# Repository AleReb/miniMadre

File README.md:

# miniMadre

**Placa de desarrollo basada en el trabajo de Sebastian Adonay con Alejandro Rebolledo.**

## Descripción del Proyecto

El objetivo de este proyecto es desarrollar una versión miniatura y flexible de una placa madre (*motherboard*) que también funcione como una placa para el **hiriPro**.

### Características Principales

*   **Versatilidad:** Diseñada para ser una solución miniatura y flexible.
*   **Integración ESP32-S3:** Se remplaza el uso de chips FTDI por el uso directo del **ESP32-S3**, aprovechando sus capacidades nativas de USB y mayor potencia de procesamiento.
*   **Expansión Flexible:** Incorpora un conector flexible diseñado específicamente para sacar placas hijo (*daughter boards*), permitiendo una gran modularidad y adaptabilidad a diferentes proyectos.

---
*Este proyecto es una evolución colaborativa buscando optimizar espacio y funcionalidad.*

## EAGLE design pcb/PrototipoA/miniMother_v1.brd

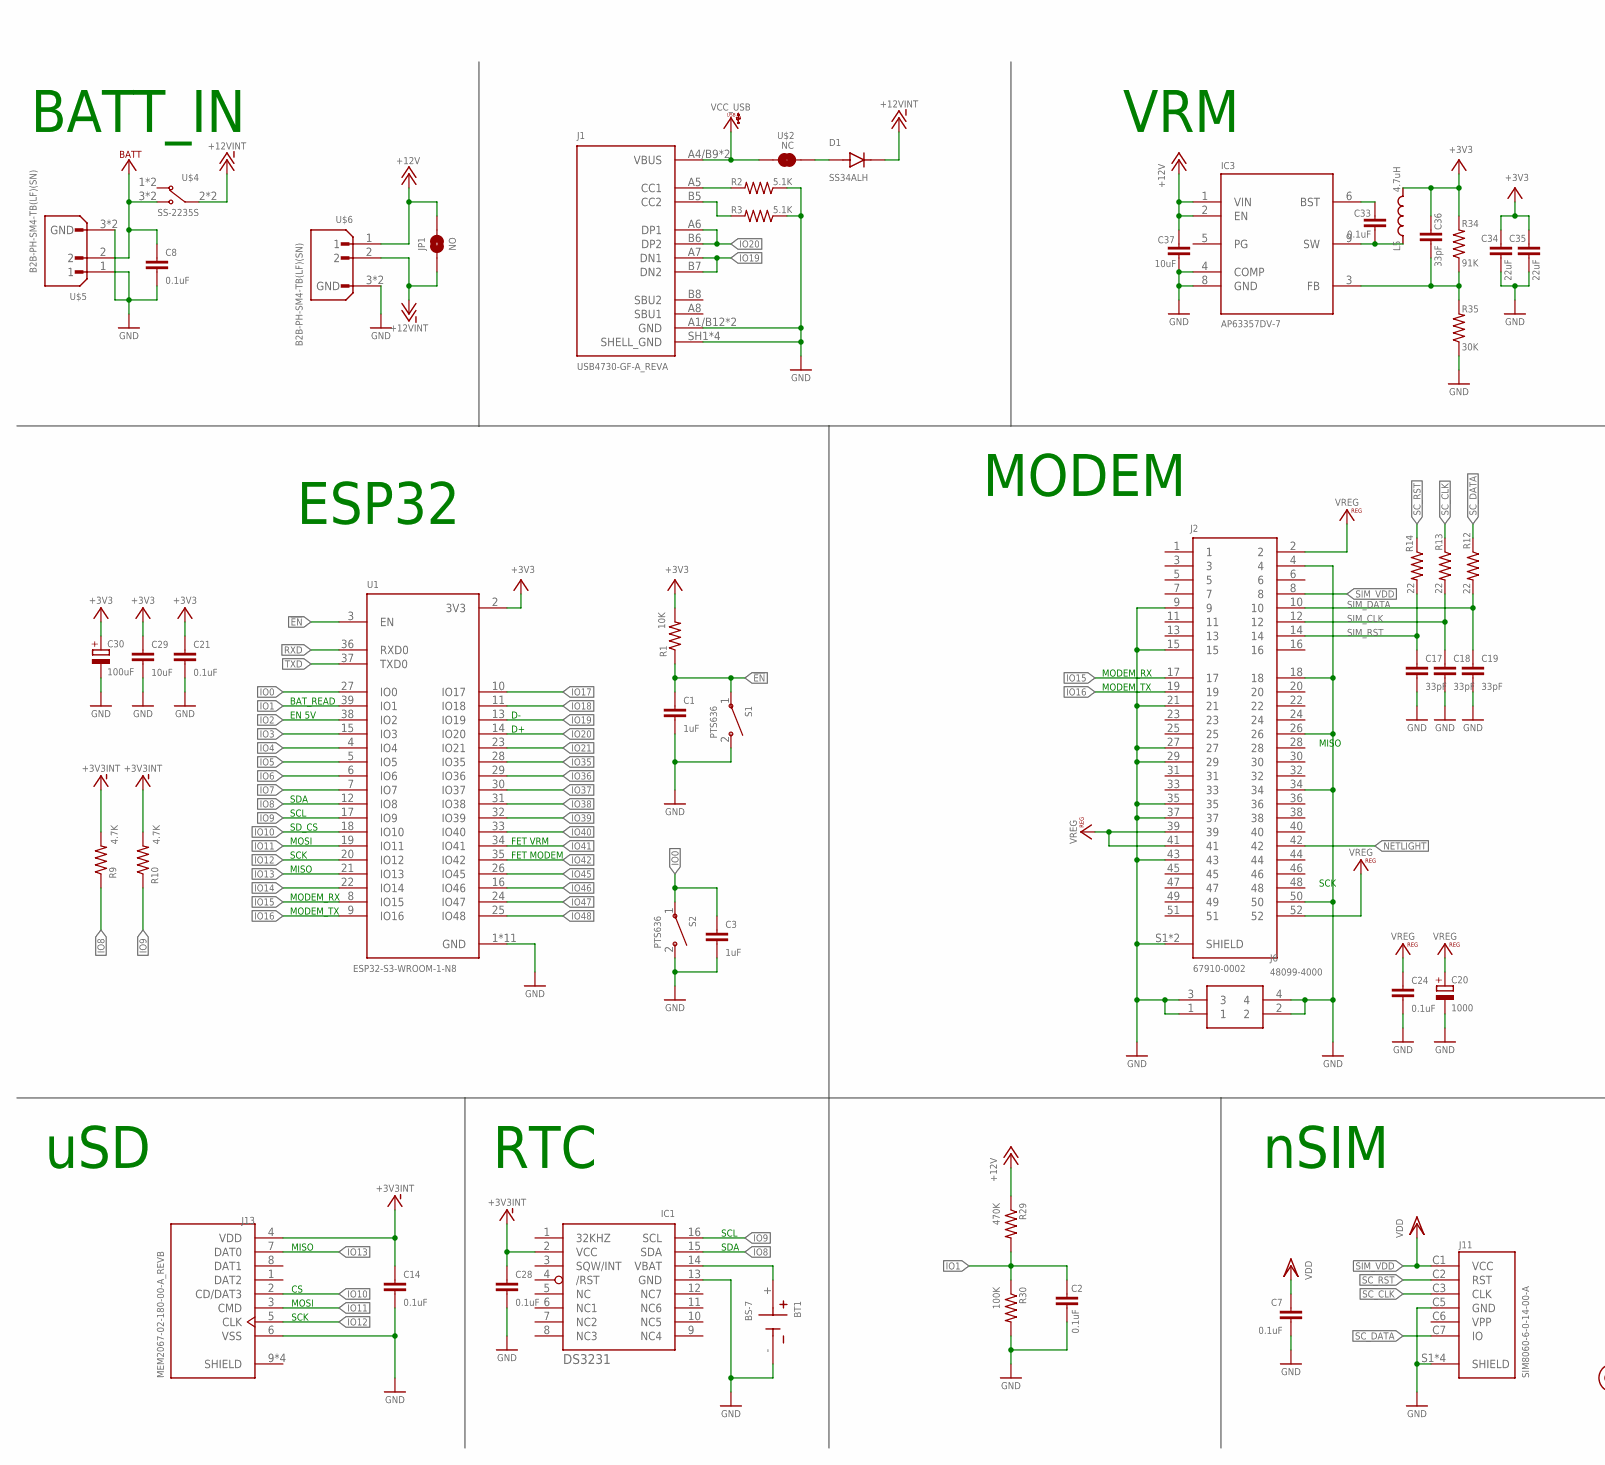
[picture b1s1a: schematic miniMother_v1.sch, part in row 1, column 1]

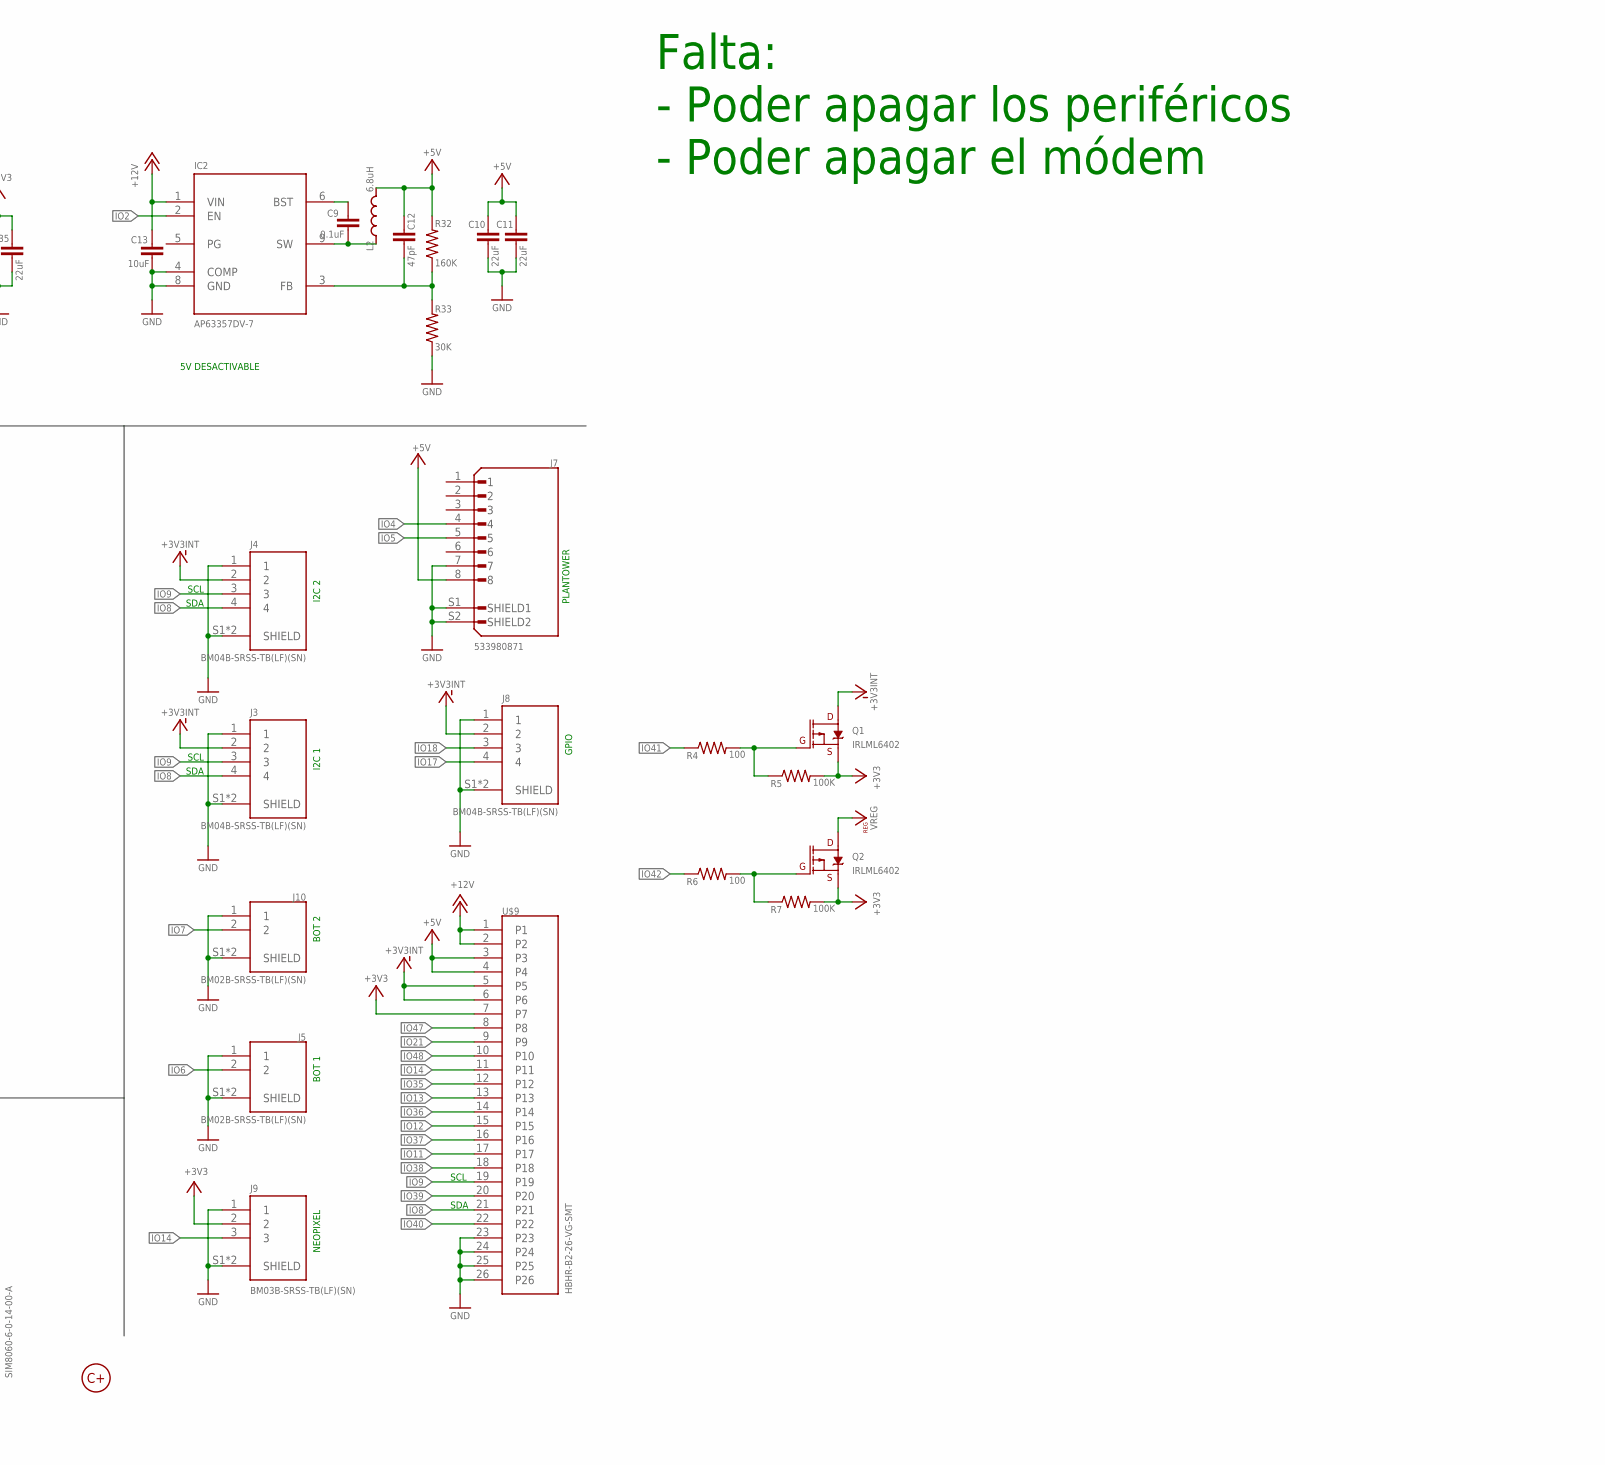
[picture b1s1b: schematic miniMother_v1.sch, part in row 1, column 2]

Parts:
BT1: BS-7; BAT_BS-7
C1, C3: 1uF; C0805
C2, C7, C8, C9, C14, C21, C24, C28, C33: 0.1uF; C0805
C10, C11, C34, C35: 22uF; C0805
C12: 47pF; C0805
C13, C29, C37: 10uF; C0805
C17, C18, C19, C36: 33pF; C0805
C20: 1000; SMC_D
C30: 100uF; CT3528
D1: SS34ALH; SODFL5226X100N
IC1: DS3231/SO; SO16W
IC2, IC3: AP63357DV-7; AP63357DV7
J1: USB4730-GF-A_REVA; GCT_USB4730-GF-A_REVA
J2: 67910-0002; MOLEX_67910-0002
J3, J4, J8: BM04B-SRSS-TB(LF)(SN); JST_BM04B-SRSS-TB(LF)(SN)
J5, J10: BM02B-SRSS-TB(LF)(SN); JST_BM02B-SRSS-TB(LF)(SN)
J6: 48099-4000; 480994000
J7: 533980871; MOLEX_533980871
J9: BM03B-SRSS-TB(LF)(SN); JST_BM03B-SRSS-TB(LF)(SN)
J11: SIM8060-6-0-14-00-A; GCT_SIM8060-6-0-14-00-A
J13: MEM2067-02-180-00-A_REVB; GCT_MEM2067-02-180-00-A_REVB
JP1: NO; SMT-JUMPER_2_NO_NO-SILK_ROUND
L2: 6.8uH; IND_MDH7045C-220MA=P3
L5: 4.7uH; IND_MDH7045C-220MA=P3
Q1, Q2: IRLML6402; SOT23-3
R1: 10K; R0805
R2, R3: 5.1K; R0805
R4, R6: 100; R0805
R5, R7, R30: 100K; R0805
R9, R10: 4.7K; R0805
R12, R13, R14: 22; R0805
R29: 470K; R0805
R32: 160K; R0805
R33, R35: 30K; R0805
R34: 91K; R0805
S1, S2: PTS636; SW_PTS636_SM43J_SMTR_LFS
U1: ESP32-S3-WROOM-1-N8; XCVR_ESP32-S3-WROOM-1-N8
U$1: LOGO_CMAS10MM; LOGO_10MM
U$2: NC; SMT-JUMPER-2_NC
U$4: SS-2235S
U$5, U$6: B2B-PH-SM4-TB(LF)(SN); JST_B2B-PH-SM4-TB(LF)(SN)
U$9: HBHR-B2-26-VG-SMT

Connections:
!EN: C1.1, R1.1, S1.1 (COM), U1.3 (EN)
+3V3: C21.1, C29.1, C30.+, C34.1, C35.1, C36.1, J9.2, L5.2, Q1.2 (S), Q2.2 (S), R1.2, R5.2, R7.2, R34.2, U1.2 (3V3), U$9.7
+3V3INT: C14.1, C28.1, IC1.2 (VCC), J3.2, J4.2, J8.2, J13.4 (VDD), Q1.3 (D), R9.2, R10.2, U$9.5, U$9.6
+5V: C10.1, C11.1, C12.1, J7.8, L2.2, R32.2, U$9.3, U$9.4
+12V: C13.1, C37.1, IC2.1 (VIN), IC3.1 (VIN), IC3.2 (EN), JP1.1, R29.1, U$6.1, U$9.1, U$9.2
+12VINT: D1.1 (K), JP1.2, U$4.2 (P1), U$4.5 (P1), U$6.2
GND: BT1.-, C1.2, C2.2, C3.2, C7.2, C8.2, C10.2, C11.2, C13.2, C14.2, C17.2, C18.2, C19.2, C20.-, C21.2, C24.2, C28.2, C29.2, C30.-, C34.2, C35.2, C37.2, IC1.13 (GND), IC2.4 (COMP), IC2.8 (GND), IC3.4 (COMP), IC3.8 (GND), J1.A1/B12 (GND), J1.B1/A12 (GND), J1.SH1 (SHELL_GND), J1.SH2 (SHELL_GND), J1.SH3 (SHELL_GND), J1.SH4 (SHELL_GND), J2.4, J2.9, J2.15, J2.18, J2.21, J2.26, J2.27, J2.29, J2.34, J2.35, J2.37, J2.43, J2.50, J2.S1 (SHIELD), J2.S2 (SHIELD), J3.1, J3.S1 (SHIELD), J3.S2 (SHIELD), J4.1, J4.S1 (SHIELD), J4.S2 (SHIELD), J5.1, J5.S1 (SHIELD), J5.S2 (SHIELD), J6.1, J6.2, J6.3, J6.4, J7.7, J7.S1 (SHIELD1), J7.S2 (SHIELD2), J8.1, J8.S1 (SHIELD), J8.S2 (SHIELD), J9.1, J9.S1 (SHIELD), J9.S2 (SHIELD), J10.1, J10.S1 (SHIELD), J10.S2 (SHIELD), J11.C5 (GND), J11.S1 (SHIELD), J11.S2 (SHIELD), J11.S3 (SHIELD), J11.S4 (SHIELD), J13.6 (VSS), R2.1, R3.1, R30.2, R33.1, R35.1, S1.2 (NO), S2.2 (NO), U1.1 (GND), U1.40 (GND), U1.41_1 (GND), U1.41_2 (GND), U1.41_3 (GND), U1.41_4 (GND), U1.41_5 (GND), U1.41_6 (GND), U1.41_7 (GND), U1.41_8 (GND), U1.41_9 (GND), U$5.1, U$5.3 (GND), U$5.4 (GND), U$6.3 (GND), U$6.4 (GND), U$9.23, U$9.24, U$9.25, U$9.26
IO0: C3.1, S2.1 (COM), U1.27 (IO0)
IO1: C2.1, R29.2, R30.1, U1.39 (IO1)
IO2: IC2.2 (EN), U1.38 (IO2)
IO3: U1.15 (IO3)
IO4: J7.4, U1.4 (IO4)
IO5: J7.5, U1.5 (IO5)
IO6: J5.2, U1.6 (IO6)
IO7: J10.2, U1.7 (IO7)
IO8: IC1.15 (SDA), J3.4, J4.4, R9.1, U1.12 (IO8), U$9.21
IO9: IC1.16 (SCL), J3.3, J4.3, R10.1, U1.17 (IO9), U$9.19
IO10: J13.2 (CD/DAT3), U1.18 (IO10)
IO11: J13.3 (CMD), U1.19 (IO11), U$9.17
IO12: J13.5 (CLK), U1.20 (IO12), U$9.15
IO13: J13.7 (DAT0), U1.21 (IO13), U$9.13
IO14: J9.3, U1.22 (IO14), U$9.11
IO15: J2.17, U1.8 (IO15)
IO16: J2.19, U1.9 (IO16)
IO17: J8.4, U1.10 (IO17)
IO18: J8.3, U1.11 (IO18)
IO19: J1.A7 (DN1), J1.B7 (DN2), U1.13 (IO19)
IO20: J1.A6 (DP1), J1.B6 (DP2), U1.14 (IO20)
IO21: U1.23 (IO21), U$9.9
IO35: U1.28 (IO35), U$9.12
IO36: U1.29 (IO36), U$9.14
IO37: U1.30 (IO37), U$9.16
IO38: U1.31 (IO38), U$9.18
IO39: U1.32 (IO39), U$9.20
IO40: U1.33 (IO40), U$9.22
IO41: R4.1, U1.34 (IO41)
IO42: R6.1, U1.35 (IO42)
IO45: U1.26 (IO45)
IO46: U1.16 (IO46)
IO47: U1.24 (IO47), U$9.8
IO48: U1.25 (IO48), U$9.10
unnamed: J1.A5 (CC1), R2.2
unnamed: BT1.+, IC1.14 (VBAT)
unnamed: D1.2 (A), U$2.2
unnamed: Q1.1 (G), R4.2, R5.1
unnamed: J1.B5 (CC2), R3.2
unnamed: Q2.1 (G), R6.2, R7.1
unnamed: C9.1, IC2.6 (BST)
unnamed: C9.2, IC2.9 (SW), L2.1
unnamed: C12.2, IC2.3 (FB), R32.1, R33.2
unnamed: C33.1, IC3.6 (BST)
unnamed: C33.2, IC3.9 (SW), L5.1
unnamed: C36.2, IC3.3 (FB), R34.1, R35.2
NETLIGHT: J2.42
RXD: U1.36 (RXD0)
SC_CLK: J11.C3 (CLK), R13.1
SC_DATA: J11.C7 (IO), R12.1
SC_RST: J11.C2 (RST), R14.1
SIM_CLK: C18.1, J2.12, R13.2
SIM_DATA: C19.1, J2.10, R12.2
SIM_RST: C17.1, J2.14, R14.2
SIM_VDD: C7.1, J2.8, J11.C1 (VCC)
TXD: U1.37 (TXD0)
VBAT: C8.1, U$4.3 (T2), U$4.6 (T2), U$5.2
VCC_USB: J1.A4/B9 (VBUS), J1.B4/A9 (VBUS), U$2.1
VREG: C20.+, C24.1, J2.2, J2.39, J2.41, J2.52, Q2.3 (D)

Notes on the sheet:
VRM
MODEM
ESP32
RTC
nSIM
uSD
BATT_IN
5V DESACTIVABLE
MOSI
SCK
MISO
PLANTOWER
Falta: - Poder apagar los periféricos - Poder apagar el módem
I2C 1
I2C 2
BOT 1
BOT 2
NEOPIXEL
GPIO
SDA
SCL
SD_CS
MODEM_RX
MODEM_TX
EN 5V
BAT_READ
FET VRM
FET MODEM

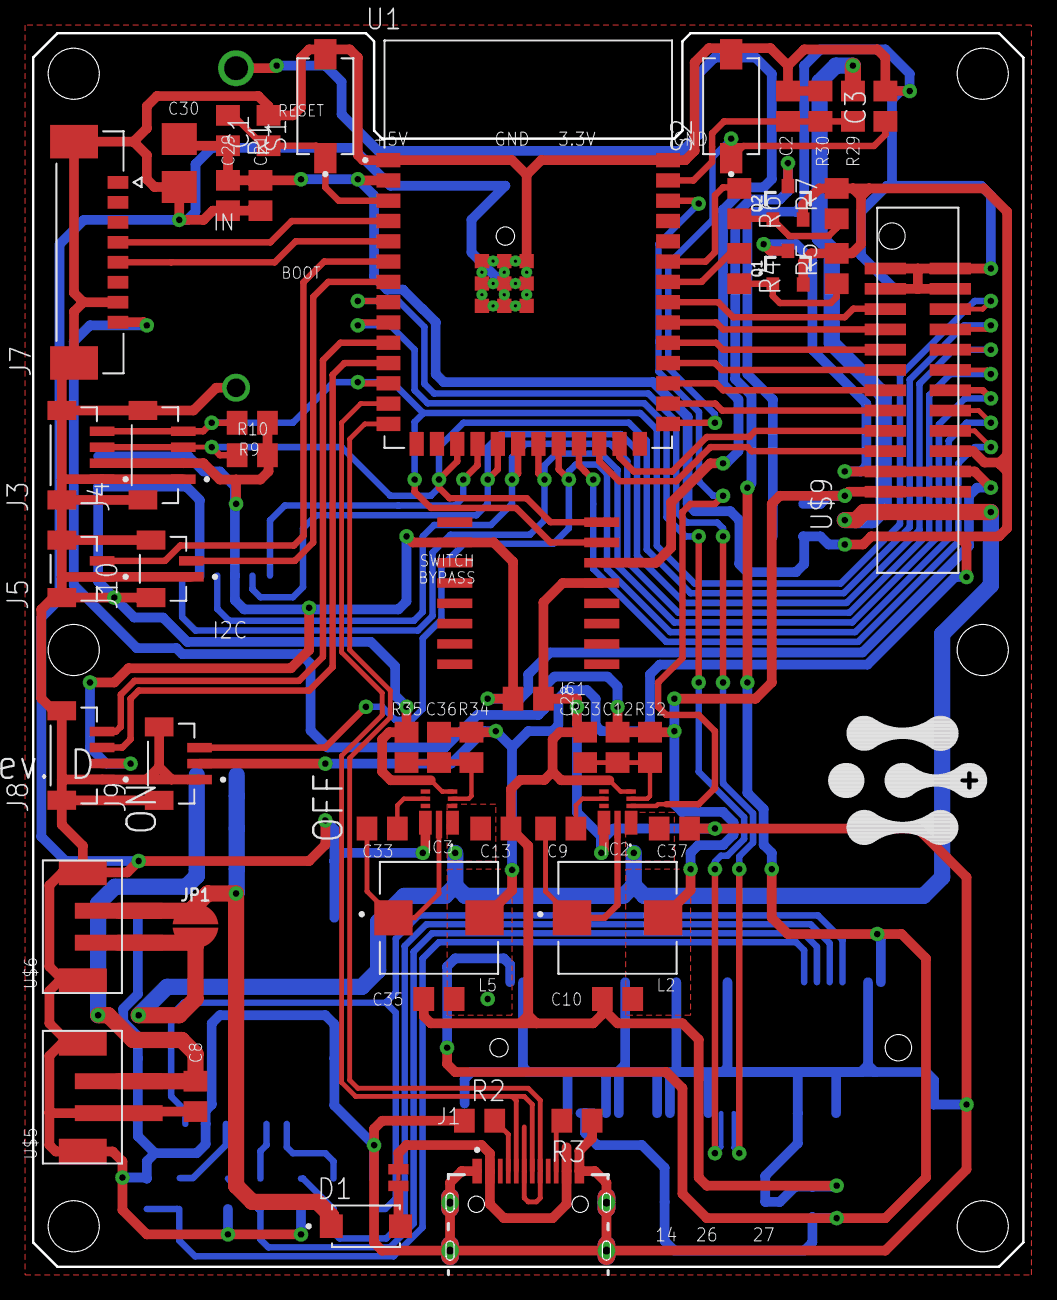
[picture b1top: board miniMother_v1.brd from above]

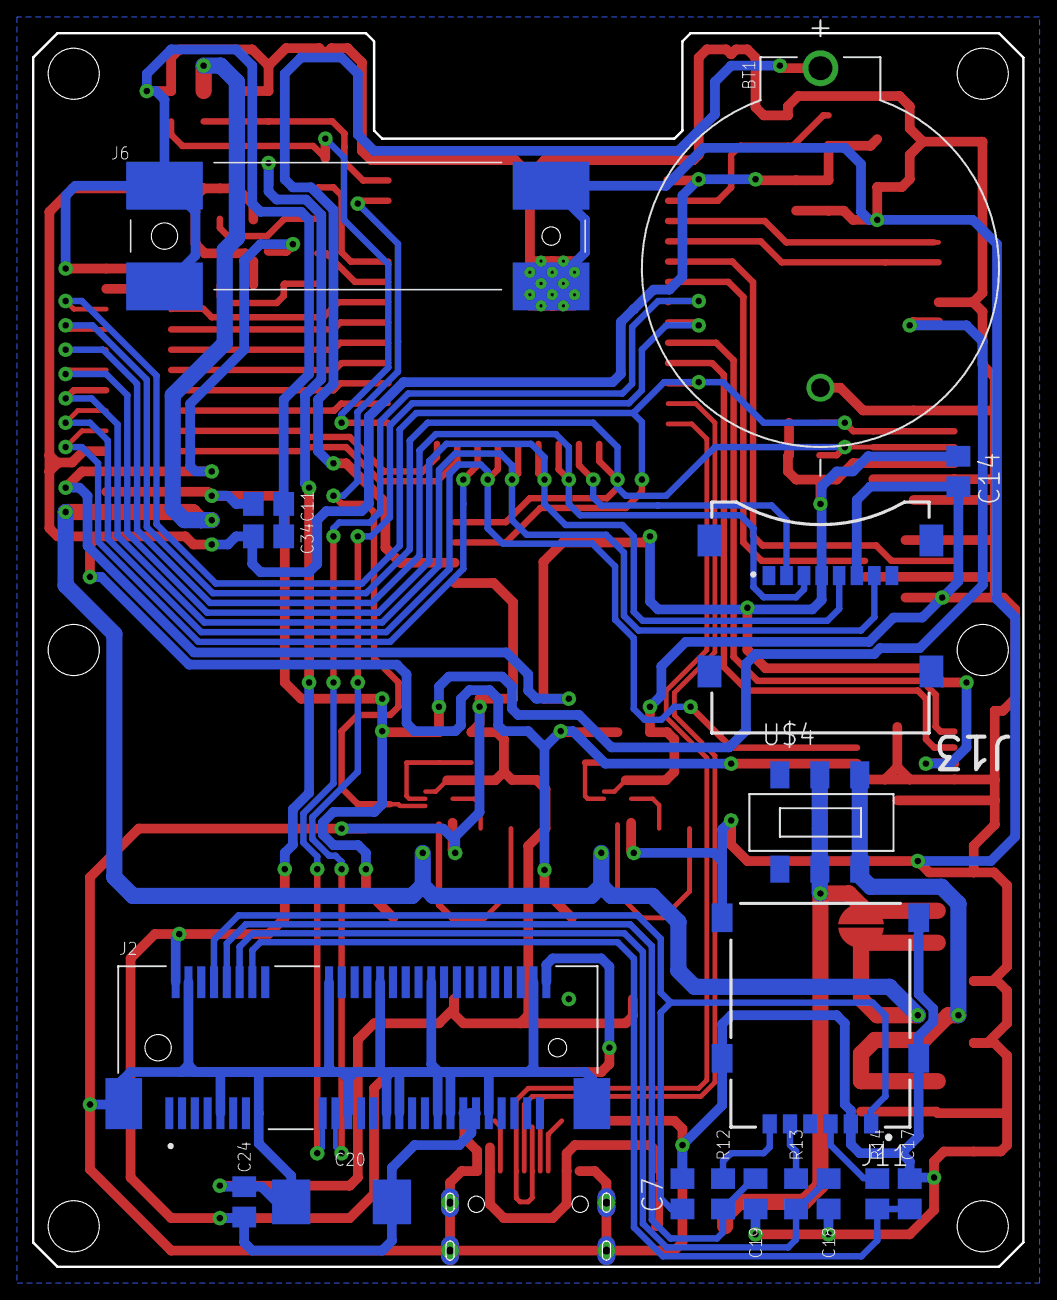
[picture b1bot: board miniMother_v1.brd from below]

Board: 2 copper layers, 62.0 x 77.2 mm, 74 parts (18 on the bottom side), 60 nets.

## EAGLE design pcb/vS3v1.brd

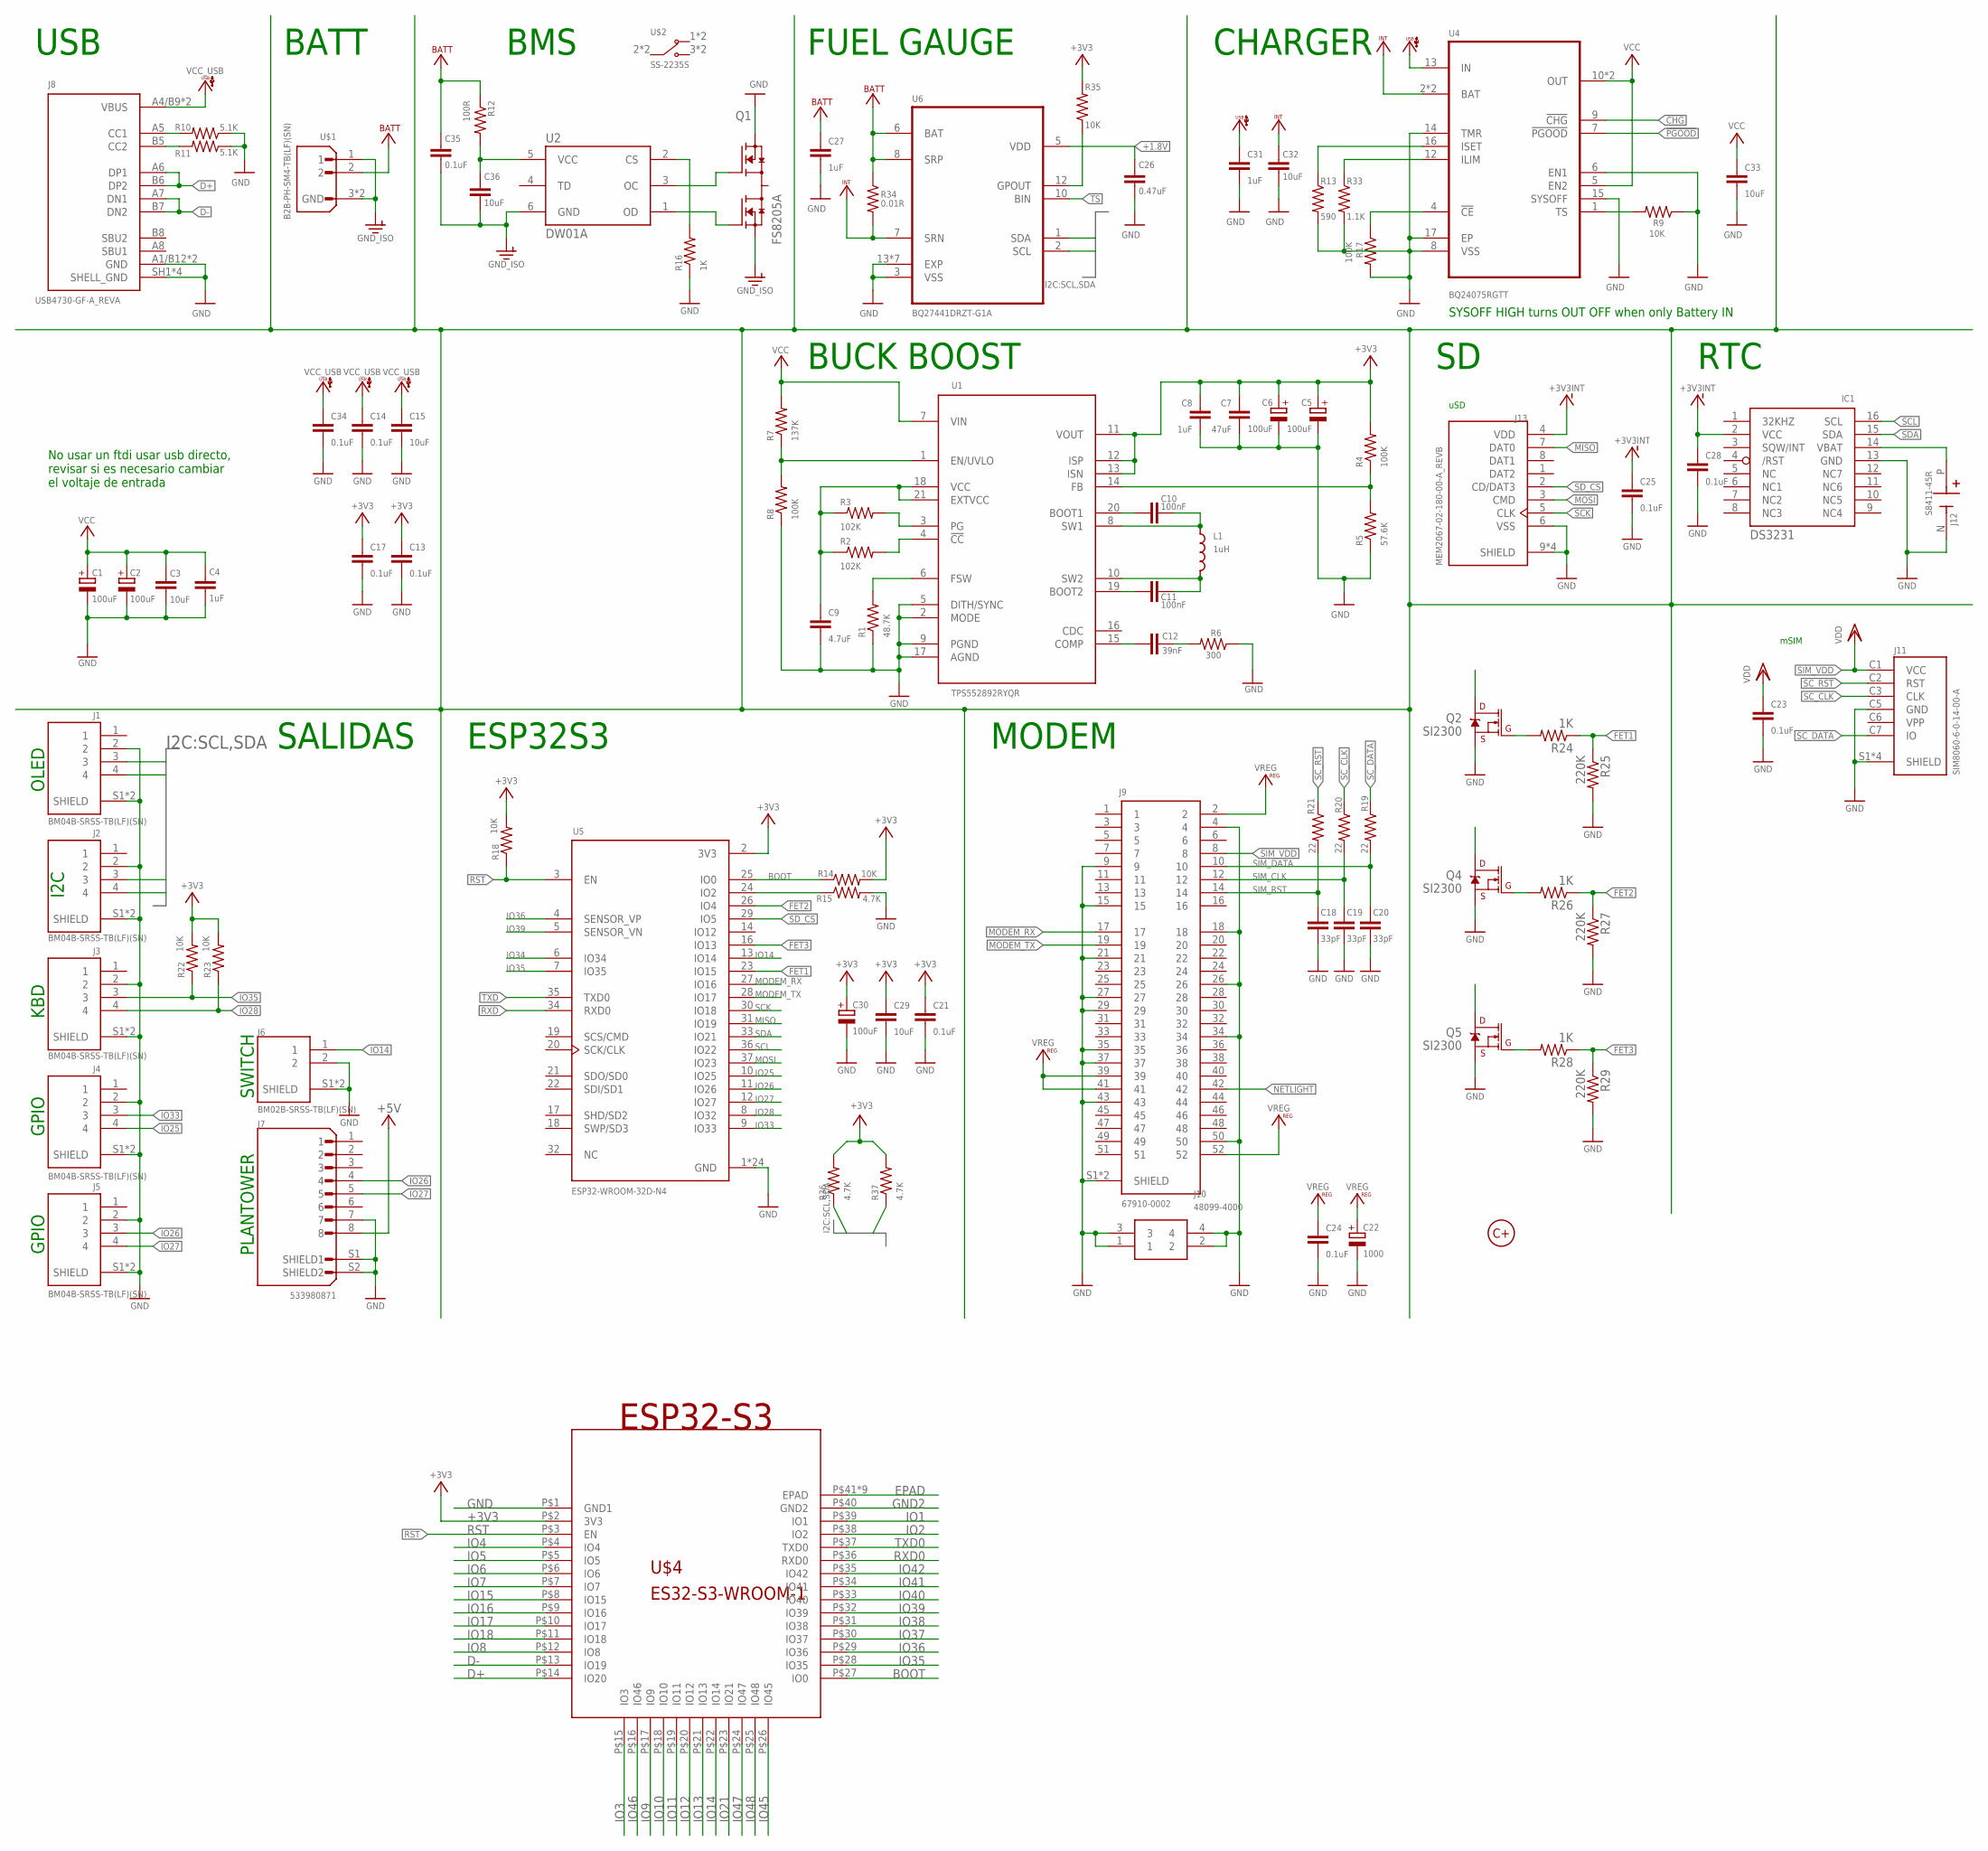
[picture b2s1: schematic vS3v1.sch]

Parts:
C1, C2, C5, C6: 100uF; SMC_B
C3, C15, C29, C32, C33, C36: 10uF; C0805
C4, C8, C27, C31: 1uF; C0805
C7: 47uF; C0805
C9: 4.7uF; C0805
C10, C11: 100nF; C0805
C12: 39nF; C0805
C13, C14, C17, C21, C23, C24, C25, C28, C34, C35: 0.1uF; C0805
C18, C19, C20: 33pF; C0805
C22: 1000; SMC_D
C26: 0.47uF; C0805
C30: 100uF; CT3528
IC1: DS3231/SO; SO16W
J1, J2, J3, J4, J5: BM04B-SRSS-TB(LF)(SN); JST_BM04B-SRSS-TB(LF)(SN)
J6: BM02B-SRSS-TB(LF)(SN); JST_BM02B-SRSS-TB(LF)(SN)
J7: 533980871; MOLEX_533980871
J8: USB4730-GF-A_REVA; GCT_USB4730-GF-A_REVA
J9: 67910-0002; MOLEX_67910-0002
J10: 48099-4000; 480994000
J11: SIM8060-6-0-14-00-A; GCT_SIM8060-6-0-14-00-A
J12: S8411-45R; HARWIN_S8411-45R
J13: MEM2067-02-180-00-A_REVB; GCT_MEM2067-02-180-00-A_REVB
L1: 1uH; IND_MDH7045C-220MA=P3
Q1: FS8205A; SOT95P280X145-6N
Q2, Q4, Q5: SI2300; SOT23-3
R1: 48.7K; R0805
R2, R3: 102K; R0805
R4, R8, R17: 100K; R0805
R5: 57.6K; R0805
R6: 300; R0805
R7: 137K; R0805
R9, R14, R18, R22, R23, R35: 10K; R0805
R10, R11: 5.1K; R0805
R12: 100R; R0805
R13: 590; R0805
R15, R36, R37: 4.7K; R0805
R16, R24, R26, R28: 1K; R0805
R19, R20, R21: 22; R0805
R25, R27, R29: 220K; R0805
R33: 1.1K; R0805
R34: 0.01R; R1206
U1: TPS552892RYQR; CONV_TPS552892RYQR
U2: DW01A; SOT23-6
U4: BQ24075RGTT; QFN50P300X300X100-17N
U5: ESP32-WROOM-32D-N4; MODULE_ESP32-WROOM-32D-N4
U6: BQ27441DRZT-G1A; IC_BQ27441DRZR-G1A
U$1: B2B-PH-SM4-TB(LF)(SN); JST_B2B-PH-SM4-TB(LF)(SN)
U$2: SS-2235S
U$3: LOGO_CMAS10MM; LOGO_10MM
U$4: ES32-S3-WROOM-1; ESP32-S3-WROOM-1

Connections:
!CHG: U4.9 (!CHG)
!PGOOD: U4.7 (!PGOOD)
+1.8V: C26.1, U6.5 (VDD)
+3V3: C5.+, C6.+, C7.1, C8.1, C13.1, C17.1, C21.1, C29.1, C30.+, R4.2, R14.2, R18.2, R22.2, R23.2, R35.2, R36.2, R37.2, U1.11 (VOUT), U1.12 (ISP), U1.13 (ISN), U5.2 (3V3), U$4.P$2 (3V3)
+3V3INT: C25.1, C28.1, IC1.2 (VCC), J13.4 (VDD)
+5V: J7.8
BOOT: R14.1, U5.25 (IO0), U$4.P$27 (IO0)
D+: J8.A6 (DP1), J8.B6 (DP2), U$4.P$14 (IO20)
D-: J8.A7 (DN1), J8.B7 (DN2), U$4.P$13 (IO19)
EPAD: U$4.P$41 (EPAD), U$4.P$42 (EPAD), U$4.P$43 (EPAD), U$4.P$44 (EPAD), U$4.P$45 (EPAD), U$4.P$46 (EPAD), U$4.P$47 (EPAD), U$4.P$48 (EPAD), U$4.P$49 (EPAD)
FET1: R24.1, R25.1, U5.23 (IO15)
FET2: R26.1, R27.1, U5.26 (IO4)
FET3: R28.1, R29.1, U5.16 (IO13)
GND: C1.-, C2.-, C3.2, C4.2, C5.-, C6.-, C7.2, C8.2, C9.2, C13.2, C14.2, C15.2, C17.2, C18.2, C19.2, C20.2, C21.2, C22.-, C23.2, C24.2, C25.2, C26.2, C27.2, C28.2, C29.2, C30.-, C31.2, C32.2, C33.2, C34.2, IC1.13 (GND), J1.2, J1.S1 (SHIELD), J1.S2 (SHIELD), J2.2, J2.S1 (SHIELD), J2.S2 (SHIELD), J3.2, J3.S1 (SHIELD), J3.S2 (SHIELD), J4.2, J4.S1 (SHIELD), J4.S2 (SHIELD), J5.2, J5.S1 (SHIELD), J5.S2 (SHIELD), J6.2, J6.S1 (SHIELD), J6.S2 (SHIELD), J7.7, J7.S1 (SHIELD1), J7.S2 (SHIELD2), J8.A1/B12 (GND), J8.B1/A12 (GND), J8.SH1 (SHELL_GND), J8.SH2 (SHELL_GND), J8.SH3 (SHELL_GND), J8.SH4 (SHELL_GND), J9.4, J9.9, J9.15, J9.18, J9.21, J9.26, J9.27, J9.29, J9.34, J9.35, J9.37, J9.43, J9.50, J9.S1 (SHIELD), J9.S2 (SHIELD), J10.1, J10.2, J10.3, J10.4, J11.C5 (GND), J11.S1 (SHIELD), J11.S2 (SHIELD), J11.S3 (SHIELD), J11.S4 (SHIELD), J12.N (-), J13.6 (VSS), J13.9 (SHIELD), J13.10 (SHIELD), J13.11 (SHIELD), J13.12 (SHIELD), Q1.3 (S2), Q2.2 (S), Q4.2 (S), Q5.2 (S), R1.1, R5.1, R6.1, R8.1, R9.1, R10.1, R11.1, R13.2, R15.2, R16.1, R17.2, R25.2, R27.2, R29.2, R33.2, U1.2 (MODE), U1.5 (DITH/SYNC), U1.9 (PGND), U1.17 (AGND), U4.6 (EN1), U4.8 (VSS), U4.14 (TMR), U4.15 (SYSOFF), U4.17 (EP), U5.1 (GND), U5.15 (GND), U5.38 (GND), U5.39_1 (GND), U5.39_2 (GND), U5.39_3 (GND), U5.39_4 (GND), U5.39_5 (GND), U5.39_6 (GND), U5.39_7 (GND), U5.39_8 (GND), U5.39_9 (GND), U5.39_10 (GND), U5.39_11 (GND), U5.39_12 (GND), U5.39_13 (GND), U5.39_14 (GND), U5.39_15 (GND), U5.39_16 (GND), U5.39_17 (GND), U5.39_18 (GND), U5.39_19 (GND), U5.39_20 (GND), U5.39_21 (GND), U6.3 (VSS), U6.13 (EXP), U6.14 (EXP), U6.15 (EXP), U6.16 (EXP), U6.17 (EXP), U6.18 (EXP), U6.19 (EXP), U$4.P$1 (GND1)
GND2: U$4.P$40 (GND2)
GND_ISO: C35.2, C36.2, Q1.1 (S1), U2.6 (GND), U$1.1, U$1.3 (GND), U$1.4 (GND)
GPOUT: R35.1, U6.12 (GPOUT)
IO1: U$4.P$39 (IO1)
IO2: U$4.P$38 (IO2)
IO3: U$4.P$15 (IO3)
IO4: U$4.P$4 (IO4)
IO5: U$4.P$5 (IO5)
IO6: U$4.P$6 (IO6)
IO7: U$4.P$7 (IO7)
IO8: U$4.P$12 (IO8)
IO9: U$4.P$17 (IO9)
IO10: U$4.P$18 (IO10)
IO11: U$4.P$19 (IO11)
IO12: U$4.P$20 (IO12)
IO13: U$4.P$21 (IO13)
IO14: J6.1, U5.13 (IO14), U$4.P$22 (IO14)
IO15: U$4.P$8 (IO15)
IO16: U$4.P$9 (IO16)
IO17: U$4.P$10 (IO17)
IO18: U$4.P$11 (IO18)
IO21: U$4.P$23 (IO21)
IO25: J4.4, U5.10 (IO25)
IO26: J5.3, J7.4, U5.11 (IO26)
IO27: J5.4, J7.5, U5.12 (IO27)
IO28: J3.4, R23.1, U5.8 (IO32)
IO33: J4.3, U5.9 (IO33)
IO34: U5.6 (IO34)
IO35: J3.3, R22.1, U5.7 (IO35), U$4.P$28 (IO35)
IO36: U5.4 (SENSOR_VP), U$4.P$29 (IO36)
IO37: U$4.P$30 (IO37)
IO38: U$4.P$31 (IO38)
IO39: U5.5 (SENSOR_VN), U$4.P$32 (IO39)
IO40: U$4.P$33 (IO40)
IO41: U$4.P$34 (IO41)
IO42: U$4.P$35 (IO42)
IO45: U$4.P$26 (IO45)
IO46: U$4.P$16 (IO46)
IO47: U$4.P$24 (IO47)
IO48: U$4.P$25 (IO48)
MISO: J13.7 (DAT0), U5.31 (IO19)
MODEM_RX: J9.17, U5.27 (IO16)
MODEM_TX: J9.19, U5.28 (IO17)
MOSI: J13.3 (CMD), U5.37 (IO23)
unnamed: R2.2, U1.4 (!CC)
unnamed: C12.1, U1.15 (COMP)
unnamed: C12.2, R6.2
unnamed: R1.2, U1.6 (FSW)
unnamed: R3.2, U1.3 (PG)
unnamed: C9.1, R2.1, R3.1, U1.18 (VCC), U1.21 (EXTVCC)
unnamed: R4.1, R5.2, U1.14 (FB)
unnamed: C11.2, L1.2, U1.10 (SW2)
unnamed: C10.1, U1.20 (BOOT1)
unnamed: C10.2, L1.1, U1.8 (SW1)
unnamed: C11.1, U1.19 (BOOT2)
unnamed: R7.1, R8.2, U1.1 (EN/UVLO)
unnamed: J8.A5 (CC1), R10.2
unnamed: J8.B5 (CC2), R11.2
unnamed: Q1.4 (G2), U2.3 (OC)
unnamed: Q1.6 (G1), U2.1 (OD)
unnamed: C36.1, R12.2, U2.5 (VCC)
unnamed: IC1.14 (VBAT), J12.P (+)
unnamed: R9.2, U4.1 (TS)
unnamed: R13.1, U4.16 (ISET)
unnamed: R33.1, U4.12 (ILIM)
unnamed: R15.1, U5.24 (IO2)
unnamed: R16.2, U2.2 (CS)
unnamed: R17.1, U4.4 (!CE)
unnamed: Q2.1 (G), R24.2
unnamed: Q4.1 (G), R26.2
unnamed: Q5.1 (G), R28.2
NETLIGHT: J9.42
RST: R18.1, U5.3 (EN), U$4.P$3 (EN)
RXD: U5.34 (RXD0)
RXD0: U$4.P$36 (RXD0)
SCK: J13.5 (CLK), U5.30 (IO18)
SCL: IC1.16 (SCL), J1.4, J2.4, R37.1, U5.36 (IO22), U6.2 (SCL)
SC_CLK: J11.C3 (CLK), R20.1
SC_DATA: J11.C7 (IO), R19.1
SC_RST: J11.C2 (RST), R21.1
SDA: IC1.15 (SDA), J1.3, J2.3, R36.1, U5.33 (IO21), U6.1 (SDA)
SD_CS: J13.2 (CD/DAT3), U5.29 (IO5)
SIM_CLK: C19.1, J9.12, R20.2
SIM_DATA: C20.1, J9.10, R19.2
SIM_RST: C18.1, J9.14, R21.2
SIM_VDD: C23.1, J9.8, J11.C1 (VCC)
TS: U6.10 (BIN)
TXD: U5.35 (TXD0)
TXD0: U$4.P$37 (TXD0)
VBAT: C27.1, C35.1, R12.1, R34.1, U6.6 (BAT), U6.8 (SRP), U$1.2
VCC: C1.+, C2.+, C3.1, C4.1, C33.1, R7.2, U1.7 (VIN), U4.5 (EN2), U4.10 (OUT), U4.11 (OUT)
VCCINT: C32.1, R34.2, U4.2 (BAT), U4.3 (BAT), U6.7 (SRN)
VCC_USB: C14.1, C15.1, C31.1, C34.1, J8.A4/B9 (VBUS), J8.B4/A9 (VBUS), U4.13 (IN)
VREG: C22.+, C24.1, J9.2, J9.39, J9.41, J9.52

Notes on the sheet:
RTC
mSIM
uSD
SYSOFF HIGH turns OUT OFF when only Battery IN
USB
BATT
BMS
FUEL GAUGE
CHARGER
SWITCH
OLED
I2C
KBD
GPIO
BUCK BOOST
SALIDAS
ESP32S3
MODEM
PLANTOWER
No usar un ftdi usar usb directo, revisar si es necesario cambiar el voltaje de entrada

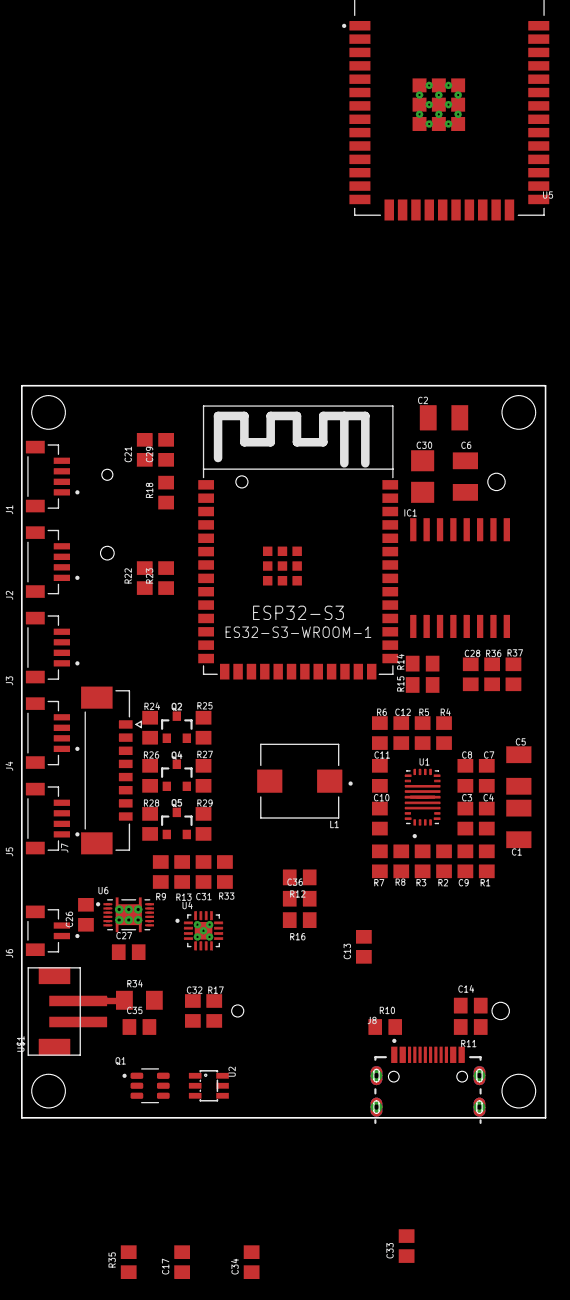
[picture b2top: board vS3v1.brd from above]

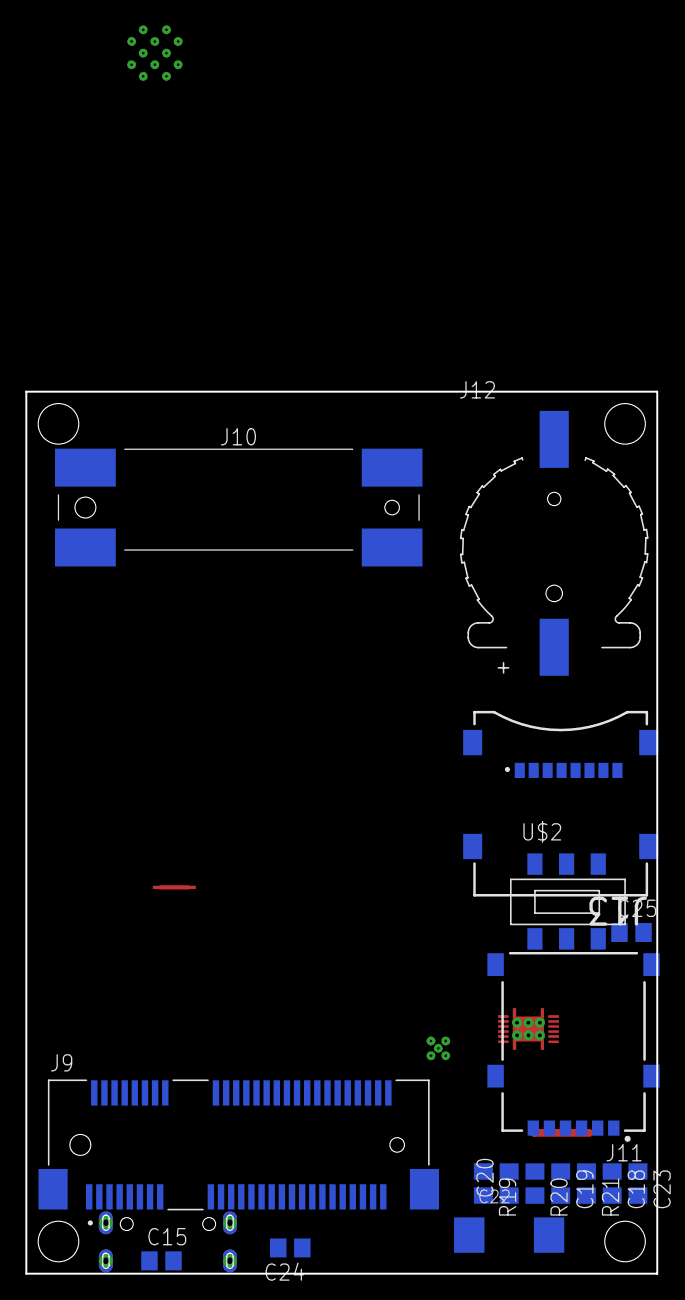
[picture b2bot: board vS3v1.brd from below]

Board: 2 copper layers, 49.8 x 69.6 mm, 97 parts (17 on the bottom side), 70 nets.

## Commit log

2026-01-18 Add datasheet link for ESP32-WROOM-32 S3
    Updated the ESP32-WROOM-32 S3 entry to include a link to its datasheet.
2026-01-18 feat: Add initial PCB design, schematic, and datasheet for miniMadre.
2026-01-18 Save local changes (PCB update, PDF remove)
2026-03-31 feat: initialize project documentation and custom LaTeX class structure

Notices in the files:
parts and their libraries:
SparkFun-Jumpers: Licensing: Creative Commons ShareAlike 4.0 International - https://creativecommons.org/licenses/by-sa/4.0
